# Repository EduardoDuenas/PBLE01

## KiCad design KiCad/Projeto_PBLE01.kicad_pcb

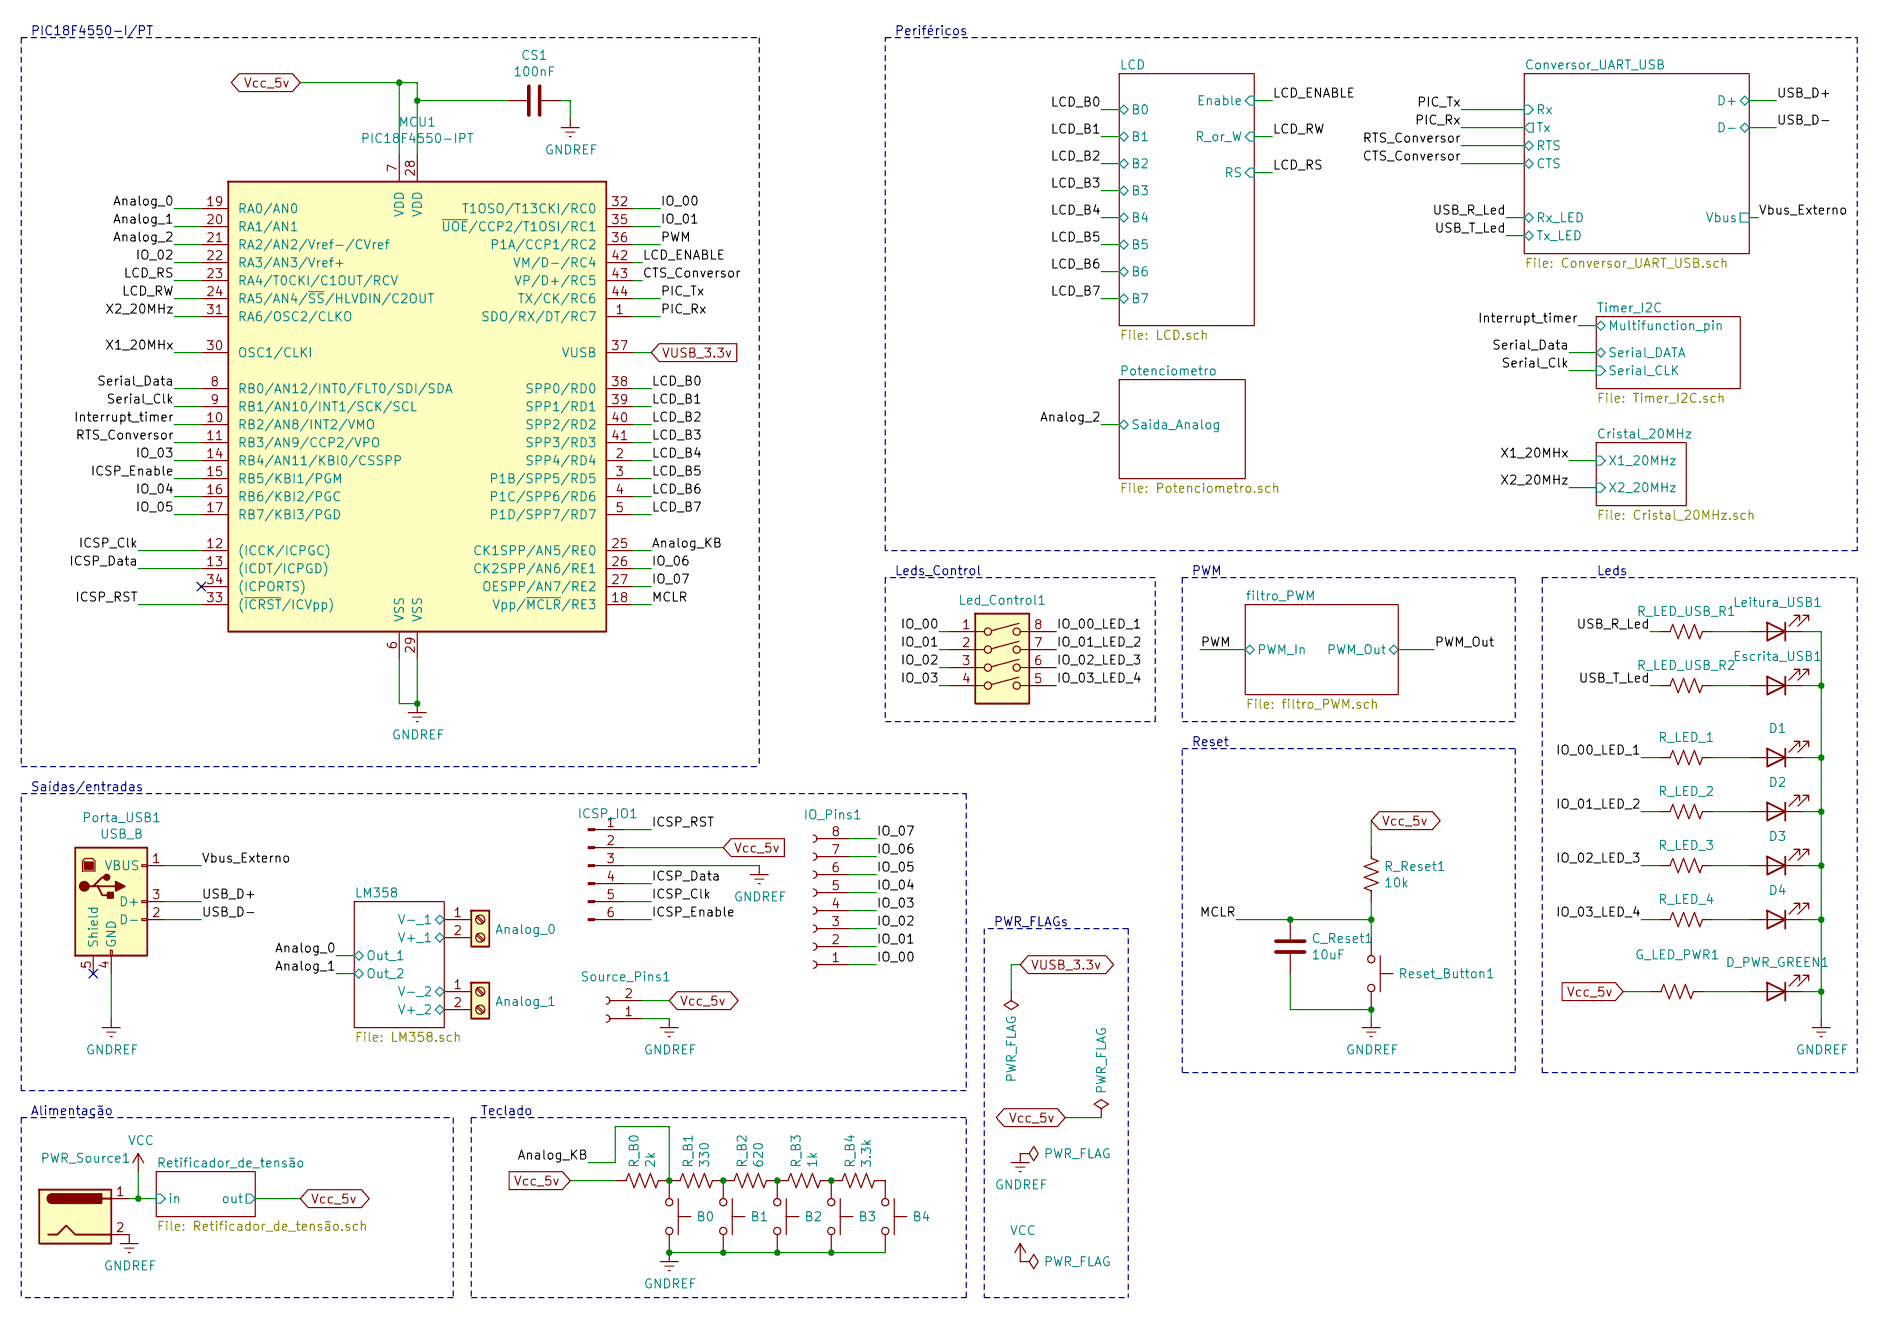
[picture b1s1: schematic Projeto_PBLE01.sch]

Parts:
Analog_0, Analog_1: Screw_Terminal_01x02; TerminalBlock_Altech_AK300-2_P5.00mm
B0, B1, B2, B3, B4: SW_Push; SW_PUSH_6mm
CS1: 100nF; C_0805_2012Metric_Pad1.18x1.45mm_HandSolder
C_Reset1: 10uF; CP_EIA-3216-18_Kemet-A_Pad1.58x1.35mm_HandSolder
D1, D2, D3, D4: LED; LED_1206_3216Metric_Pad1.42x1.75mm_HandSolder
D_PWR_GREEN1: G_LED; LED_1206_3216Metric_Pad1.42x1.75mm_HandSolder
Escrita_USB1: LED; LED_1206_3216Metric_Pad1.42x1.75mm_HandSolder
G_LED_PWR1: 200; LED_1206_3216Metric
ICSP_IO1: Conn_01x06_Male; PinHeader_1x06_P1.00mm_Vertical
IO_Pins1: Conn_01x08_Female; PinHeader_1x08_P1.00mm_Vertical
Led_Control1: SW_DIP_x04; DIP4PIN
Leitura_USB1: LED; LED_1206_3216Metric_Pad1.42x1.75mm_HandSolder
MCU1: PIC18F4550-IPT; TQFP-44_10x10mm_P0.8mm
PWR_Source1: Jack-DC; PJ-002A
Porta_USB1: USB_B; USB_B_OST_USB-B1HSxx_Horizontal
R_B0: 2k; R_0805_2012Metric
R_B1: 330; R_0805_2012Metric
R_B2: 620; R_0805_2012Metric
R_B3: 1k; R_0805_2012Metric
R_B4: 3.3k; R_0805_2012Metric
R_LED_1, R_LED_2, R_LED_3, R_LED_4: 100; R_0805_2012Metric
R_LED_USB_R1, R_LED_USB_R2: 100; R_0805_2012Metric
R_Reset1: 10k; R_0805_2012Metric
Reset_Button1: SW_Push; SW_PUSH_6mm
Source_Pins1: Conn_01x02_Female; PinHeader_1x02_P1.00mm_Vertical

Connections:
/Analog_0: MCU1.19 (RA0/AN0); also elsewhere on the board
/Analog_1: MCU1.20 (RA1/AN1); also elsewhere on the board
/Analog_2: MCU1.21 (RA2/AN2/Vref-/CVref); also elsewhere on the board
/Analog_KB: B0.1, MCU1.25 (CK1SPP/AN5/RE0), R_B0.2, R_B1.1
/CTS_Conversor: MCU1.43 (VP/D+/RC5); also elsewhere on the board
/ICSP_Clk: ICSP_IO1.5, MCU1.12 ((ICCK/ICPGC))
/ICSP_Data: ICSP_IO1.4, MCU1.13 ((ICDT/ICPGD))
/ICSP_Enable: ICSP_IO1.6, MCU1.15 (RB5/KBI1/PGM)
/ICSP_RST: ICSP_IO1.1, MCU1.33 ((~ICRST~/ICVpp))
/IO_00: IO_Pins1.1, Led_Control1.1, MCU1.32 (T1OSO/T13CKI/RC0)
/IO_00_LED_1: Led_Control1.8, R_LED_1.2
/IO_01: IO_Pins1.2, Led_Control1.2, MCU1.35 (~UOE~/CCP2/T1OSI/RC1)
/IO_01_LED_2: Led_Control1.7, R_LED_2.2
/IO_02: IO_Pins1.3, Led_Control1.3, MCU1.22 (RA3/AN3/Vref+)
/IO_02_LED_3: Led_Control1.6, R_LED_3.2
/IO_03: IO_Pins1.4, Led_Control1.4, MCU1.14 (RB4/AN11/KBI0/CSSPP)
/IO_03_LED_4: Led_Control1.5, R_LED_4.2
/IO_04: IO_Pins1.5, MCU1.16 (RB6/KBI2/PGC)
/IO_05: IO_Pins1.6, MCU1.17 (RB7/KBI3/PGD)
/IO_06: IO_Pins1.7, MCU1.26 (CK2SPP/AN6/RE1)
/IO_07: IO_Pins1.8, MCU1.27 (OESPP/AN7/RE2)
/Interrupt_timer: MCU1.10 (RB2/AN8/INT2/VMO); also elsewhere on the board
/LCD_B0: MCU1.38 (SPP0/RD0); also elsewhere on the board
/LCD_B1: MCU1.39 (SPP1/RD1); also elsewhere on the board
/LCD_B2: MCU1.40 (SPP2/RD2); also elsewhere on the board
/LCD_B3: MCU1.41 (SPP3/RD3); also elsewhere on the board
/LCD_B4: MCU1.2 (SPP4/RD4); also elsewhere on the board
/LCD_B5: MCU1.3 (P1B/SPP5/RD5); also elsewhere on the board
/LCD_B6: MCU1.4 (P1C/SPP6/RD6); also elsewhere on the board
/LCD_B7: MCU1.5 (P1D/SPP7/RD7); also elsewhere on the board
/LCD_ENABLE: MCU1.42 (VM/D-/RC4); also elsewhere on the board
/LCD_RS: MCU1.23 (RA4/T0CKI/C1OUT/RCV); also elsewhere on the board
/LCD_RW: MCU1.24 (RA5/AN4/~SS~/HLVDIN/C2OUT); also elsewhere on the board
/LM358/V+_1: Analog_0.2; also elsewhere on the board
/LM358/V+_2: Analog_1.2; also elsewhere on the board
/LM358/V-_1: Analog_0.1; also elsewhere on the board
/LM358/V-_2: Analog_1.1; also elsewhere on the board
/MCLR: C_Reset1.1, MCU1.18 (Vpp/~MCLR~/RE3), R_Reset1.2, Reset_Button1.1
/PIC_Rx: MCU1.1 (SDO/RX/DT/RC7); also elsewhere on the board
/PIC_Tx: MCU1.44 (TX/CK/RC6); also elsewhere on the board
/PWM: MCU1.36 (P1A/CCP1/RC2); also elsewhere on the board
/RTS_Conversor: MCU1.11 (RB3/AN9/CCP2/VPO); also elsewhere on the board
/Serial_Clk: MCU1.9 (RB1/AN10/INT1/SCK/SCL); also elsewhere on the board
/Serial_Data: MCU1.8 (RB0/AN12/INT0/FLT0/SDI/SDA); also elsewhere on the board
/USB_D+: Porta_USB1.3 (D+); also elsewhere on the board
/USB_D-: Porta_USB1.2 (D-); also elsewhere on the board
/USB_R_Led: R_LED_USB_R1.2; also elsewhere on the board
/USB_T_Led: R_LED_USB_R2.2; also elsewhere on the board
/Vbus_Externo: Porta_USB1.1 (VBUS); also elsewhere on the board
/X1_20MHx: MCU1.30 (OSC1/CLKI); also elsewhere on the board
/X2_20MHz: MCU1.31 (RA6/OSC2/CLKO); also elsewhere on the board
GNDREF: B0.2, B1.2, B2.2, B3.2, B4.2, CS1.1, C_Reset1.2, D1.1 (K), D2.1 (K), D3.1 (K), D4.1 (K), D_PWR_GREEN1.1 (K), Escrita_USB1.1 (K), ICSP_IO1.3, Leitura_USB1.1 (K), MCU1.6 (VSS), MCU1.29 (VSS), PWR_Source1.2, PWR_Source1.3, Porta_USB1.4 (GND), Reset_Button1.2, Source_Pins1.1; also elsewhere on the board
unnamed: B1.1, R_B1.2, R_B2.1
unnamed: B2.1, R_B2.2, R_B3.1
unnamed: B3.1, R_B3.2, R_B4.1
unnamed: B4.1, R_B4.2
unnamed: D1.2 (A), R_LED_1.1
unnamed: D2.2 (A), R_LED_2.1
unnamed: D3.2 (A), R_LED_3.1
unnamed: D4.2 (A), R_LED_4.1
unnamed: D_PWR_GREEN1.2 (A), G_LED_PWR1.1
unnamed: Escrita_USB1.2 (A), R_LED_USB_R2.1
unnamed: Leitura_USB1.2 (A), R_LED_USB_R1.1
VCC: PWR_Source1.1; also elsewhere on the board
VUSB_3.3v: MCU1.37 (VUSB)
Vcc_5v: CS1.2, G_LED_PWR1.2, ICSP_IO1.2, MCU1.7 (VDD), MCU1.28 (VDD), R_B0.1, R_Reset1.1, Source_Pins1.2; also elsewhere on the board

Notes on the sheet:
Saídas/entradas
Alimentação
PIC18F4550-I/PT
Reset
Leds
Teclado
Periféricos
PWR_FLAGs
PWM
Leds_Control

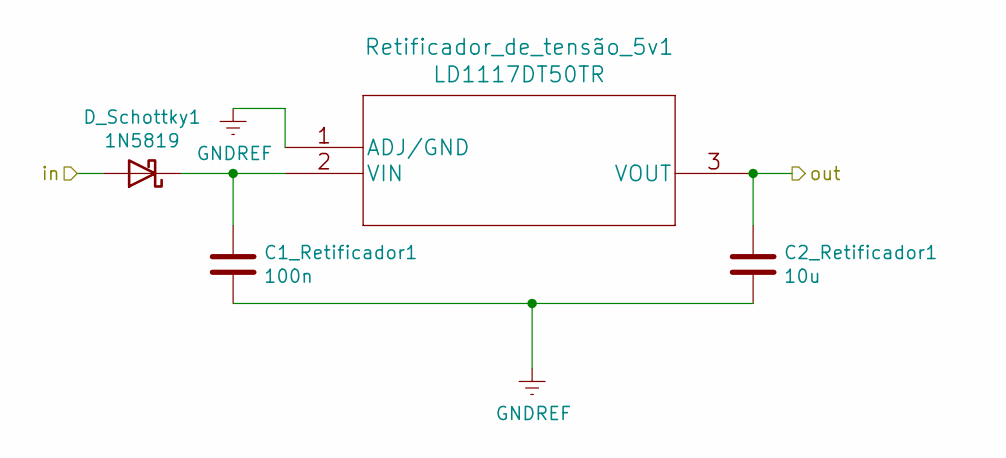
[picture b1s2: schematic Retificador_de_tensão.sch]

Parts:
C1_Retificador1: 100n; C_0805_2012Metric_Pad1.18x1.45mm_HandSolder
C2_Retificador1: 10u; CP_EIA-3216-18_Kemet-A_Pad1.58x1.35mm_HandSolder
D_Schottky1: 1N5819; D_DO-41_SOD81_P10.16mm_Horizontal
Retificador_de_tensão_5v1: LD1117DT50TR; TO-252-3_TabPin2

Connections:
GNDREF: C1_Retificador1.2, C2_Retificador1.2, Retificador_de_tensão_5v1.1 (ADJ/GND); also elsewhere on the board
unnamed: C1_Retificador1.1, D_Schottky1.1 (K), Retificador_de_tensão_5v1.2 (VIN)
VCC: D_Schottky1.2 (A); also elsewhere on the board
Vcc_5v: C2_Retificador1.1, Retificador_de_tensão_5v1.3 (VOUT); also elsewhere on the board

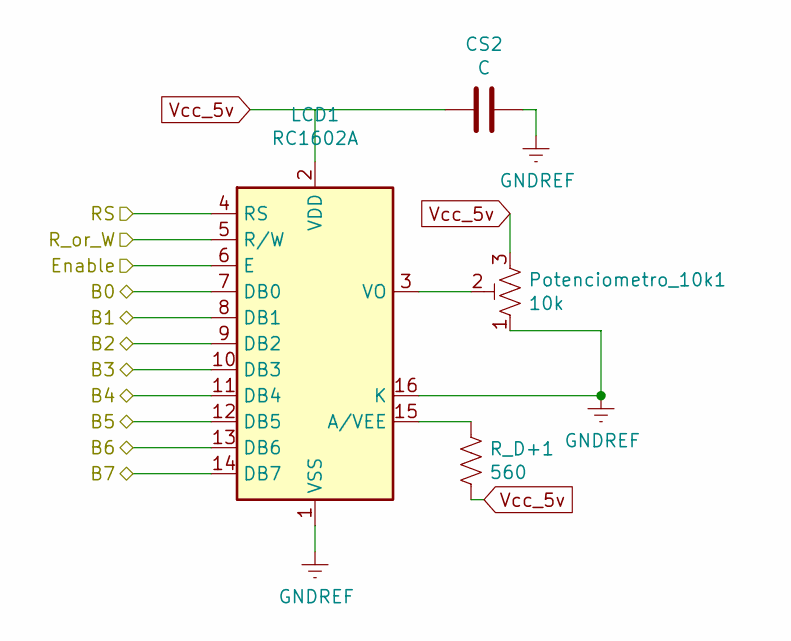
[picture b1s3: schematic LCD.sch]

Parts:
CS2: C; C_0805_2012Metric_Pad1.18x1.45mm_HandSolder
LCD1: RC1602A; WC1602A
Potenciometro_10k1: 10k; Potentiometer_Bourns_3296W_Vertical
R_D+1: 560; R_0805_2012Metric

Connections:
/LCD_B0: LCD1.7 (DB0); also elsewhere on the board
/LCD_B1: LCD1.8 (DB1); also elsewhere on the board
/LCD_B2: LCD1.9 (DB2); also elsewhere on the board
/LCD_B3: LCD1.10 (DB3); also elsewhere on the board
/LCD_B4: LCD1.11 (DB4); also elsewhere on the board
/LCD_B5: LCD1.12 (DB5); also elsewhere on the board
/LCD_B6: LCD1.13 (DB6); also elsewhere on the board
/LCD_B7: LCD1.14 (DB7); also elsewhere on the board
/LCD_ENABLE: LCD1.6 (E); also elsewhere on the board
/LCD_RS: LCD1.4 (RS); also elsewhere on the board
/LCD_RW: LCD1.5 (R/W); also elsewhere on the board
GNDREF: CS2.1, LCD1.1 (VSS), LCD1.16 (K), Potenciometro_10k1.1; also elsewhere on the board
unnamed: LCD1.3 (VO), Potenciometro_10k1.2
unnamed: LCD1.15 (A/VEE), R_D+1.1
Vcc_5v: CS2.2, LCD1.2 (VDD), Potenciometro_10k1.3, R_D+1.2; also elsewhere on the board

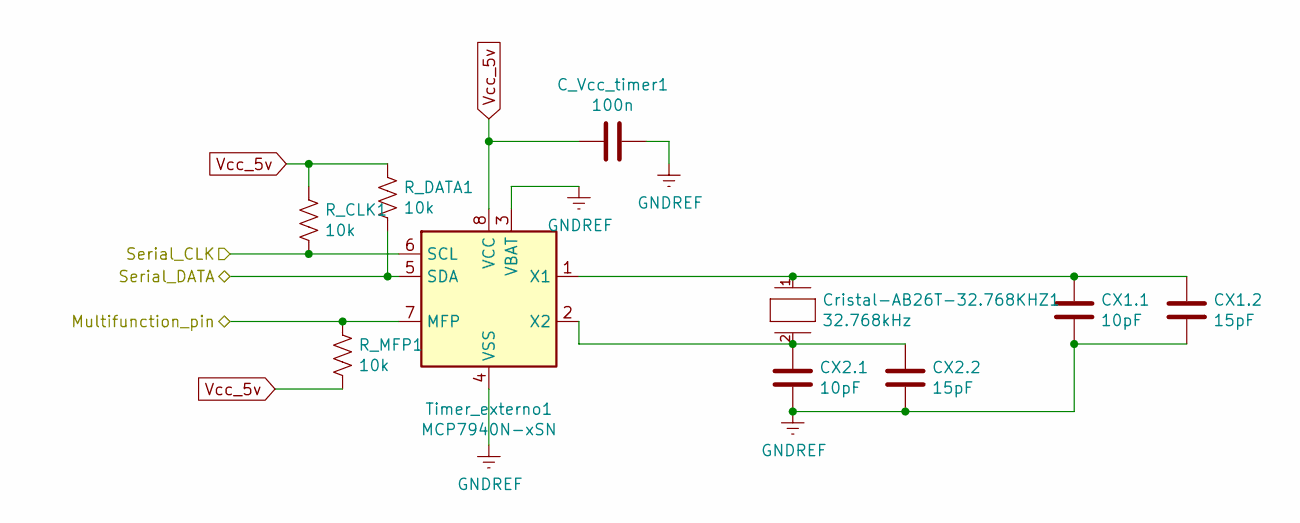
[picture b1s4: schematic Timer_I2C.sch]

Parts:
CX1.1, CX2.1: 10pF; C_0805_2012Metric_Pad1.18x1.45mm_HandSolder
CX1.2, CX2.2: 15pF; C_0805_2012Metric_Pad1.18x1.45mm_HandSolder
C_Vcc_timer1: 100n; C_0805_2012Metric_Pad1.18x1.45mm_HandSolder
Cristal-AB26T-32.768KHZ1: 32.768kHz; Frequency Tolerance ±20ppm; mouser part number 815-AB26T-32.768KHZ; digikey description 32.768kHz ±20ppm Crystal 12.5pF 35 kOhm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
R_CLK1: 10k; R_0805_2012Metric
R_DATA1: 10k; R_0805_2012Metric
R_MFP1: 10k; R_0805_2012Metric
Timer_externo1: MCP7940N-xSN

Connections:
/Interrupt_timer: R_MFP1.1, Timer_externo1.7 (MFP); also elsewhere on the board
/Serial_Clk: R_CLK1.2, Timer_externo1.6 (SCL); also elsewhere on the board
/Serial_Data: R_DATA1.2, Timer_externo1.5 (SDA); also elsewhere on the board
GNDREF: CX1.1.2, CX1.2.2, CX2.1.1, CX2.2.2, C_Vcc_timer1.1, Timer_externo1.3 (VBAT), Timer_externo1.4 (VSS); also elsewhere on the board
unnamed: CX1.1.1, CX1.2.1, Cristal-AB26T-32.768KHZ1.1, Timer_externo1.1 (X1)
unnamed: CX2.1.2, CX2.2.1, Cristal-AB26T-32.768KHZ1.2, Timer_externo1.2 (X2)
Vcc_5v: C_Vcc_timer1.2, R_CLK1.1, R_DATA1.1, R_MFP1.2, Timer_externo1.8 (VCC); also elsewhere on the board

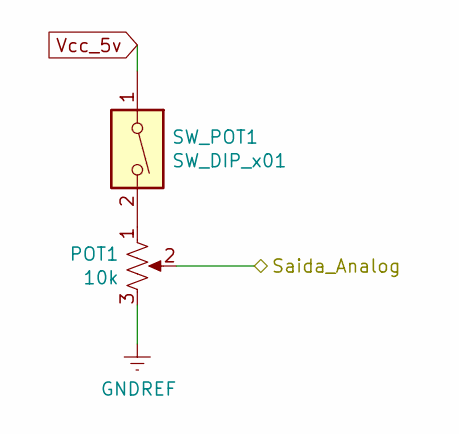
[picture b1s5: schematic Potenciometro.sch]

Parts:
POT1: 10k; Potentiometer_Piher_T-16H_Single_Horizontal
SW_POT1: SW_DIP_x01; DIP1PIN

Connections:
/Analog_2: POT1.2; also elsewhere on the board
GNDREF: POT1.3; also elsewhere on the board
unnamed: POT1.1, SW_POT1.2
Vcc_5v: SW_POT1.1; also elsewhere on the board

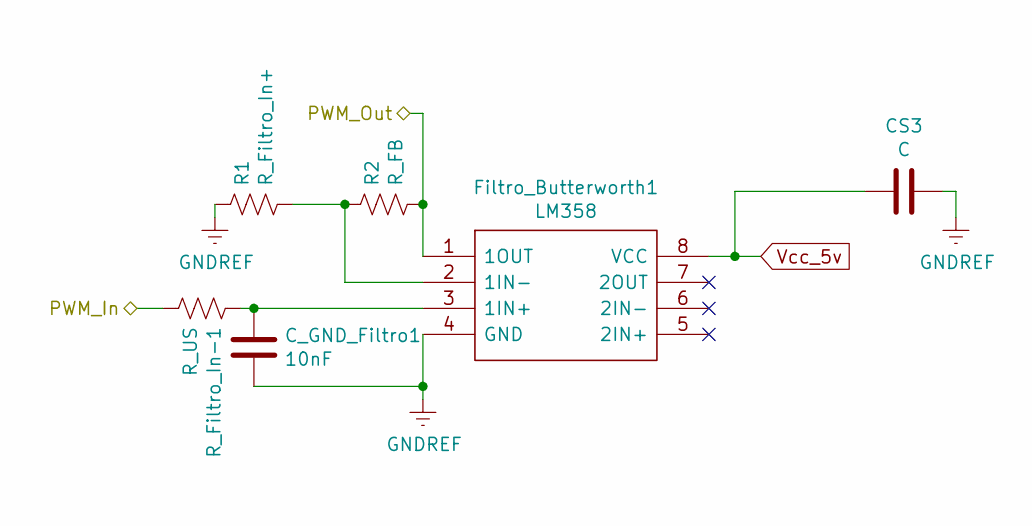
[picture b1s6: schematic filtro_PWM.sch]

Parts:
CS3: C; C_0805_2012Metric_Pad1.18x1.45mm_HandSolder
C_GND_Filtro1: 10nF; C_0805_2012Metric_Pad1.18x1.45mm_HandSolder
Filtro_Butterworth1: LM358; SOIC-8_3.9x4.9mm_P1.27mm; Manufacturer_Part_Number LM358
R1: R_Filtro_In+; R_0805_2012Metric
R2: R_FB; R_0805_2012Metric
R_Filtro_In-1: R_US; R_0805_2012Metric

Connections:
/PWM: R_Filtro_In-1.2; also elsewhere on the board
/PWM_Out: Filtro_Butterworth1.1 (1OUT), R2.2
GNDREF: CS3.1, C_GND_Filtro1.2, Filtro_Butterworth1.4 (GND), R1.1; also elsewhere on the board
unnamed: C_GND_Filtro1.1, Filtro_Butterworth1.3 (1IN+), R_Filtro_In-1.1
unnamed: Filtro_Butterworth1.2 (1IN-), R1.2, R2.1
Vcc_5v: CS3.2, Filtro_Butterworth1.8 (VCC); also elsewhere on the board

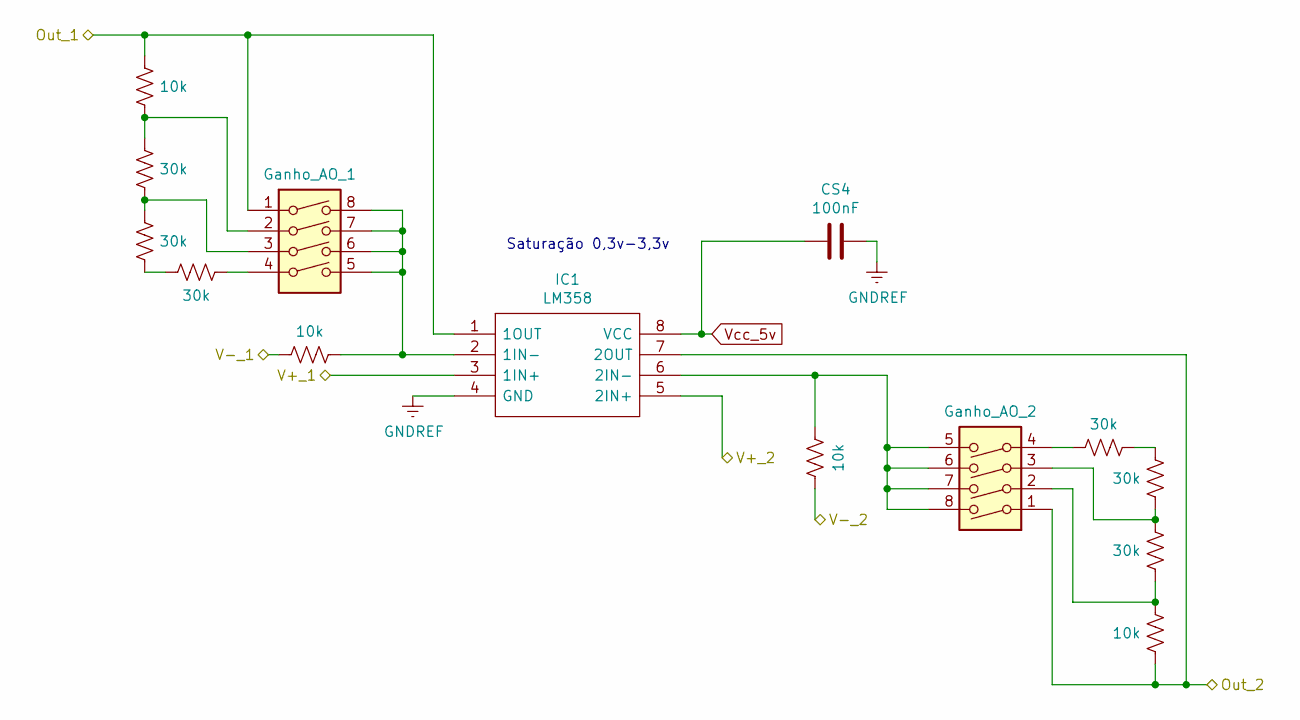
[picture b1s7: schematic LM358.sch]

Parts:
CS4: 100nF; C_0805_2012Metric_Pad1.18x1.45mm_HandSolder
Ganho_AO_1, Ganho_AO_2: SW_DIP_x04; DIP4PIN
IC1: LM358; SOIC-8_3.9x4.9mm_P1.27mm; Manufacturer_Part_Number LM358
R1_AO_1, R1_AO_2, R2_10k_AO_1, R2_10k_AO_2: 10k; R_0805_2012Metric
R2_30k_2_AO_1, R2_30k_2_AO_2, R2_30k_3_AO_1, R2_30k_3_AO_2, R2_30k_AO_1, R2_30k_AO_2: 30k; R_0805_2012Metric

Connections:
/Analog_0: Ganho_AO_1.1, IC1.1 (1OUT), R2_10k_AO_1.1; also elsewhere on the board
/Analog_1: Ganho_AO_2.1, IC1.7 (2OUT), R2_10k_AO_2.2; also elsewhere on the board
/LM358/V+_1: IC1.3 (1IN+); also elsewhere on the board
/LM358/V+_2: IC1.5 (2IN+); also elsewhere on the board
/LM358/V-_1: R1_AO_1.2; also elsewhere on the board
/LM358/V-_2: R1_AO_2.1; also elsewhere on the board
GNDREF: CS4.1, IC1.4 (GND); also elsewhere on the board
unnamed: Ganho_AO_1.2, R2_10k_AO_1.2, R2_30k_AO_1.1
unnamed: Ganho_AO_1.3, R2_30k_2_AO_1.1, R2_30k_AO_1.2
unnamed: Ganho_AO_1.4, R2_30k_3_AO_1.2
unnamed: Ganho_AO_1.5, Ganho_AO_1.6, Ganho_AO_1.7, Ganho_AO_1.8, IC1.2 (1IN-), R1_AO_1.1
unnamed: Ganho_AO_2.2, R2_10k_AO_2.1, R2_30k_AO_2.1
unnamed: Ganho_AO_2.3, R2_30k_2_AO_2.1, R2_30k_AO_2.2
unnamed: Ganho_AO_2.4, R2_30k_3_AO_2.1
unnamed: Ganho_AO_2.5, Ganho_AO_2.6, Ganho_AO_2.7, Ganho_AO_2.8, IC1.6 (2IN-), R1_AO_2.2
unnamed: R2_30k_2_AO_1.2, R2_30k_3_AO_1.1
unnamed: R2_30k_2_AO_2.2, R2_30k_3_AO_2.2
Vcc_5v: CS4.2, IC1.8 (VCC); also elsewhere on the board

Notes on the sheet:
Saturação 0,3v-3,3v

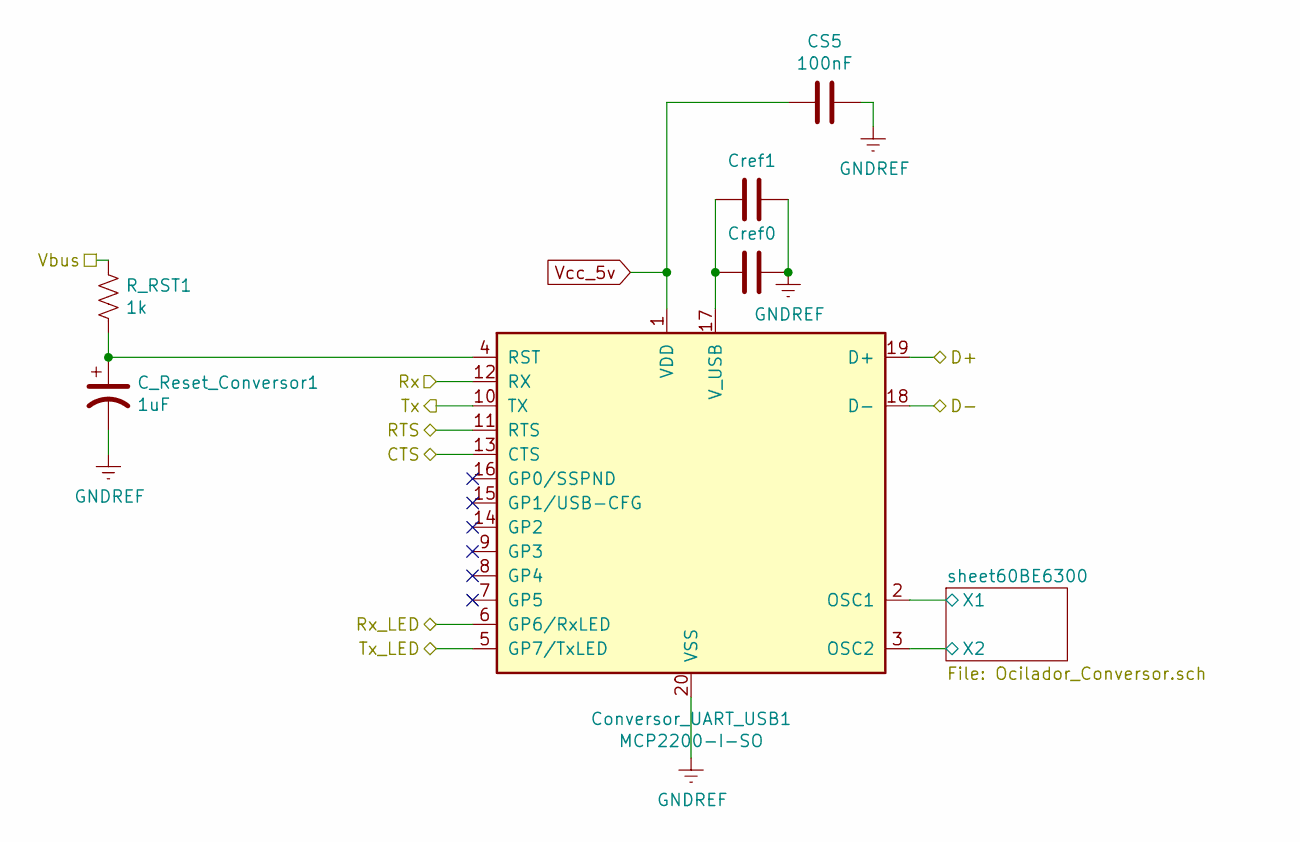
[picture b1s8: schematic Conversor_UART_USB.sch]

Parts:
CS5: 100nF; C_0805_2012Metric_Pad1.18x1.45mm_HandSolder
C_Reset_Conversor1: 1uF; CP_EIA-6032-28_Kemet-C_Pad2.25x2.35mm_HandSolder
Conversor_UART_USB1: MCP2200-I-SO; SOIC-20W_7.5x12.8mm_P1.27mm
Cref0, Cref1: 10uF; CP_EIA-3216-18_Kemet-A_Pad1.58x1.35mm_HandSolder
R_RST1: 1k; R_0805_2012Metric

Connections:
/CTS_Conversor: Conversor_UART_USB1.13 (CTS); also elsewhere on the board
/Conversor_UART_USB/sheet60BE6300/X1: Conversor_UART_USB1.2 (OSC1); also elsewhere on the board
/Conversor_UART_USB/sheet60BE6300/X2: Conversor_UART_USB1.3 (OSC2); also elsewhere on the board
/PIC_Rx: Conversor_UART_USB1.10 (TX); also elsewhere on the board
/PIC_Tx: Conversor_UART_USB1.12 (RX); also elsewhere on the board
/RTS_Conversor: Conversor_UART_USB1.11 (RTS); also elsewhere on the board
/USB_D+: Conversor_UART_USB1.19 (D+); also elsewhere on the board
/USB_D-: Conversor_UART_USB1.18 (D-); also elsewhere on the board
/USB_R_Led: Conversor_UART_USB1.6 (GP6/RxLED); also elsewhere on the board
/USB_T_Led: Conversor_UART_USB1.5 (GP7/TxLED); also elsewhere on the board
/Vbus_Externo: R_RST1.1; also elsewhere on the board
GNDREF: CS5.1, C_Reset_Conversor1.2, Conversor_UART_USB1.20 (VSS), Cref0.1, Cref1.1; also elsewhere on the board
unnamed: C_Reset_Conversor1.1, Conversor_UART_USB1.4 (RST), R_RST1.2
unnamed: Conversor_UART_USB1.17 (V_USB), Cref0.2, Cref1.2
Vcc_5v: CS5.2, Conversor_UART_USB1.1 (VDD); also elsewhere on the board

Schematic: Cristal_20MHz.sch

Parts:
CX1_20MHz1, CX2_20MHz1: 15pF
Cristal_20MHz1: 20MHz

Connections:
/X1_20MHx: CX1_20MHz1.2, Cristal_20MHz1.1; also elsewhere on the board
/X2_20MHz: CX2_20MHz1.2, Cristal_20MHz1.2; also elsewhere on the board
GNDREF: CX1_20MHz1.1, CX2_20MHz1.1; also elsewhere on the board

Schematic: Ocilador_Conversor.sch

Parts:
C1, C2: 22pF; C_0805_2012Metric_Pad1.18x1.45mm_HandSolder
Crystal_12MHz: 12MHz

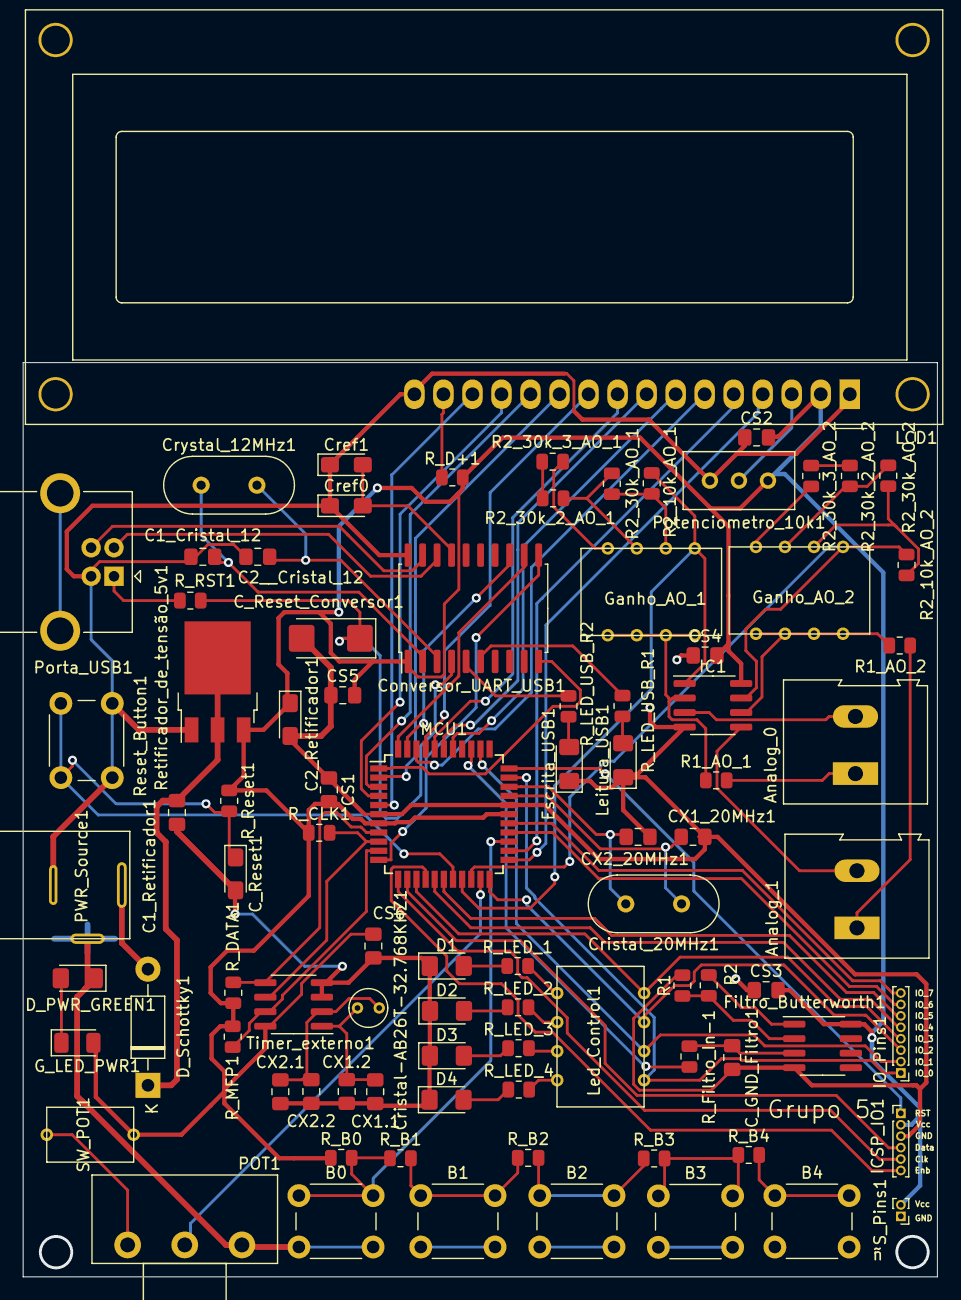
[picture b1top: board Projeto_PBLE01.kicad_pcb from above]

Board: 2 copper layers, 80.0 x 80.0 mm, 89 parts (0 on the bottom side), 88 nets.

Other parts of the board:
C1_Cristal_12, C2__Cristal_12: 22pF; C_0805_2012Metric_Pad1.18x1.45mm_HandSolder
CS6: 100n; C_0805_2012Metric_Pad1.18x1.45mm_HandSolder
Crystal_12MHz1: 12MHz; Crystal_HC49-4H_Vertical
S_Pins1: Conn_01x02_Female; PinHeader_1x02_P1.00mm_Vertical

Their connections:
/Conversor_UART_USB/sheet60BE6300/X1: C1_Cristal_12.1, Crystal_12MHz1.1; also elsewhere on the board
/Conversor_UART_USB/sheet60BE6300/X2: C2__Cristal_12.1, Crystal_12MHz1.2; also elsewhere on the board
GNDREF: C1_Cristal_12.2, C2__Cristal_12.2, CS6.1, S_Pins1.1; also elsewhere on the board
Vcc_5v: CS6.2, S_Pins1.2; also elsewhere on the board

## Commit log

2021-05-23 teste
2021-05-23 teste1.1
2021-05-23 Revert "teste1.1"
    This reverts commit a9861cd5b266b3988834488315d6e07dbdbb0367.
2021-05-23 Revert "Revert "teste1.1""
    This reverts commit 6b531b4424982b4ded159c9a2db51d3a41a741f6.
2021-05-23 Revert "Merge branch 'main' of https://github.com/EduardoDuenas/PBLE01 into main"
    This reverts commit 9a71280a43de2c009adc09aa3a7293361a0fda06, reversing
    changes made to ae6c77bb40d1ae6f6efaeae59efb69416e5190d8.
2021-05-23 Revert "teste"
    This reverts commit ae6c77bb40d1ae6f6efaeae59efb69416e5190d8.
2021-05-23 Safe_point
2021-05-24 24/05
2021-05-25 25/05
2021-05-26 26/05
2021-05-27 PWM and minor changes
    Filtro Butterworth e conexão dos LED's
2021-05-27 v1_final
2021-06-10 correção do RST do conversor
2021-06-18 correção da avaliação cruzada
2021-06-22 Finalização do esquemático
2021-07-05 adição departe dos footprints
2021-07-07 adição de mais footprints
2021-07-08 100% atualizado
2021-07-08 pble_zip
2021-07-08 trilhas
2021-07-08 começo da pcb
2021-07-08 componentes pbc
2021-07-08 adição do plano de terra e furos de fixação
2021-07-16 PCB resolução dos erros
2021-07-18 ajuste da PCB
2021-07-20 correção P1: LCD e Capacitores
2021-07-26 Valores dos capacitores CS
2021-07-26 correções de trilha
2021-08-09 Rbutterworth
2021-08-09 rled
